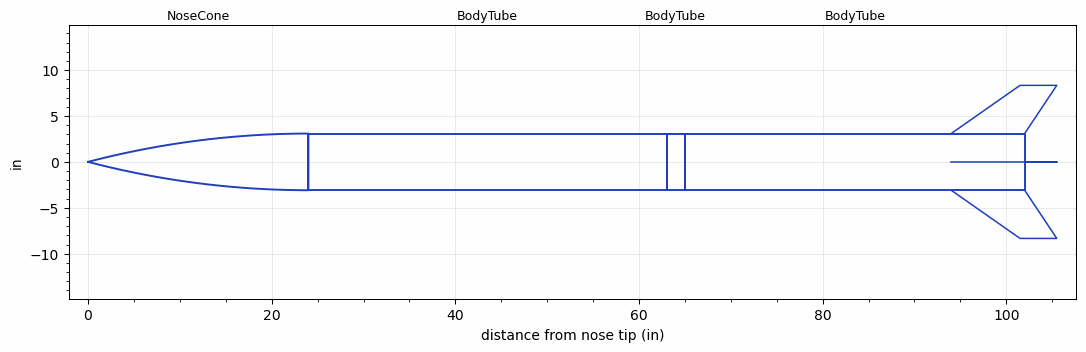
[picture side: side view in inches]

<RASAeroDocument>
 <FileVersion>2</FileVersion>
 <RocketDesign>
  <NoseCone>
   <Length>24</Length>
   <Diameter>6.17</Diameter>
   <Shape>Tangent Ogive</Shape>
   <Location>0</Location>
  </NoseCone>
  <BodyTube>
   <Length>39</Length>
   <Diameter>6.17</Diameter>
   <Location>24</Location>
  </BodyTube>
  <BodyTube>
   <Length>2</Length>
   <Diameter>6.17</Diameter>
   <Location>63</Location>
  </BodyTube>
  <BodyTube>
   <Length>37</Length>
   <Diameter>6.17</Diameter>
   <Location>65</Location>
   <Fin>
    <Count>4</Count>
    <Chord>8</Chord>
    <Span>5.25</Span>
    <SweepDistance>7.5</SweepDistance>
    <TipChord>4</TipChord>
    <Thickness>0.125</Thickness>
    <Location>8</Location>
    <AirfoilSection>Square</AirfoilSection>
   </Fin>
  </BodyTube>
  <Surface>Smooth Paint</Surface>
  <ModifiedBarrowman>False</ModifiedBarrowman>
  <Turbulence>False</Turbulence>
  <UseBooster1>False</UseBooster1>
  <UseBooster2>False</UseBooster2>
 </RocketDesign>
 <LaunchSite>
  <Altitude>7</Altitude>
  <Pressure>30.16</Pressure>
  <RodAngle>0</RodAngle>
  <RodLength>5</RodLength>
  <Temperature>60</Temperature>
  <WindSpeed>20</WindSpeed>
 </LaunchSite>
 <Recovery>
  <Altitude1>1000</Altitude1>
  <Altitude2>800</Altitude2>
  <DeviceType1>Parachute</DeviceType1>
  <DeviceType2>Parachute</DeviceType2>
  <Event1>True</Event1>
  <Event2>True</Event2>
  <Size1>18</Size1>
  <Size2>96</Size2>
  <EventType1>Apogee</EventType1>
  <EventType2>Altitude</EventType2>
  <CD1>1.55</CD1>
  <CD2>1.55</CD2>
 </Recovery>
 <SimulationList>
  <Simulation>
   <SustainerEngine>L1390G  (Aerotech)</SustainerEngine>
   <SustainerLaunchWt>44.6</SustainerLaunchWt>
   <SustainerNozzleDiameter>1.25</SustainerNozzleDiameter>
   <SustainerCG>60.81</SustainerCG>
   <SustainerIgnitionDelay>0</SustainerIgnitionDelay>
   <Booster1SeparationDelay>0</Booster1SeparationDelay>
   <Booster1IgnitionDelay>0</Booster1IgnitionDelay>
   <IncludeBooster1>False</IncludeBooster1>
   <Booster2Delay>0</Booster2Delay>
   <IncludeBooster2>False</IncludeBooster2>
   <TimetoApogee>17.0803</TimetoApogee>
   <MaxAltitude>4385.693</MaxAltitude>
   <MaxVelocity>562.0992</MaxVelocity>
   <OptimumWt>4.815</OptimumWt>
   <OptimumMaxAlt>4.815</OptimumMaxAlt>
  </Simulation>
  <Simulation>
   <SustainerEngine>L1520T  (AT)</SustainerEngine>
   <SustainerLaunchWt>42.6</SustainerLaunchWt>
   <SustainerNozzleDiameter>2.4</SustainerNozzleDiameter>
   <SustainerCG>64.97</SustainerCG>
   <SustainerIgnitionDelay>0</SustainerIgnitionDelay>
   <Booster1SeparationDelay>0</Booster1SeparationDelay>
   <Booster1IgnitionDelay>0</Booster1IgnitionDelay>
   <IncludeBooster1>False</IncludeBooster1>
   <Booster2Delay>0</Booster2Delay>
   <IncludeBooster2>False</IncludeBooster2>
   <TimetoApogee>17.1303</TimetoApogee>
   <MaxAltitude>4507.163</MaxAltitude>
   <MaxVelocity>571.7906</MaxVelocity>
  </Simulation>
 </SimulationList>
</RASAeroDocument>
